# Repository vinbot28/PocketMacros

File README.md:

# PocketMacros
A minimalist macro pad with 11 switches, a rotary encoder, and a display 0.91in OLED.

## CAD
Case was designed in onshape, and the macropad uses a "budget" gasket style mount, sandwiching the PCB. Uses 4 screws to mate the top and bottom casings together.

## PCB
Here is the schematic and PCB:

## BOM
- 1x Seeed XIAO RP2040
- 11x MX-Style switches
- 12x 1N4148 diodes
- 11x Blank DSA keycaps
- 1x 0.91 inch OLED display
- 1x EC11 Rotary encoder
- 4x M3x5mx4mm heat set inserts
- 4x M3x12mm screws (owned)

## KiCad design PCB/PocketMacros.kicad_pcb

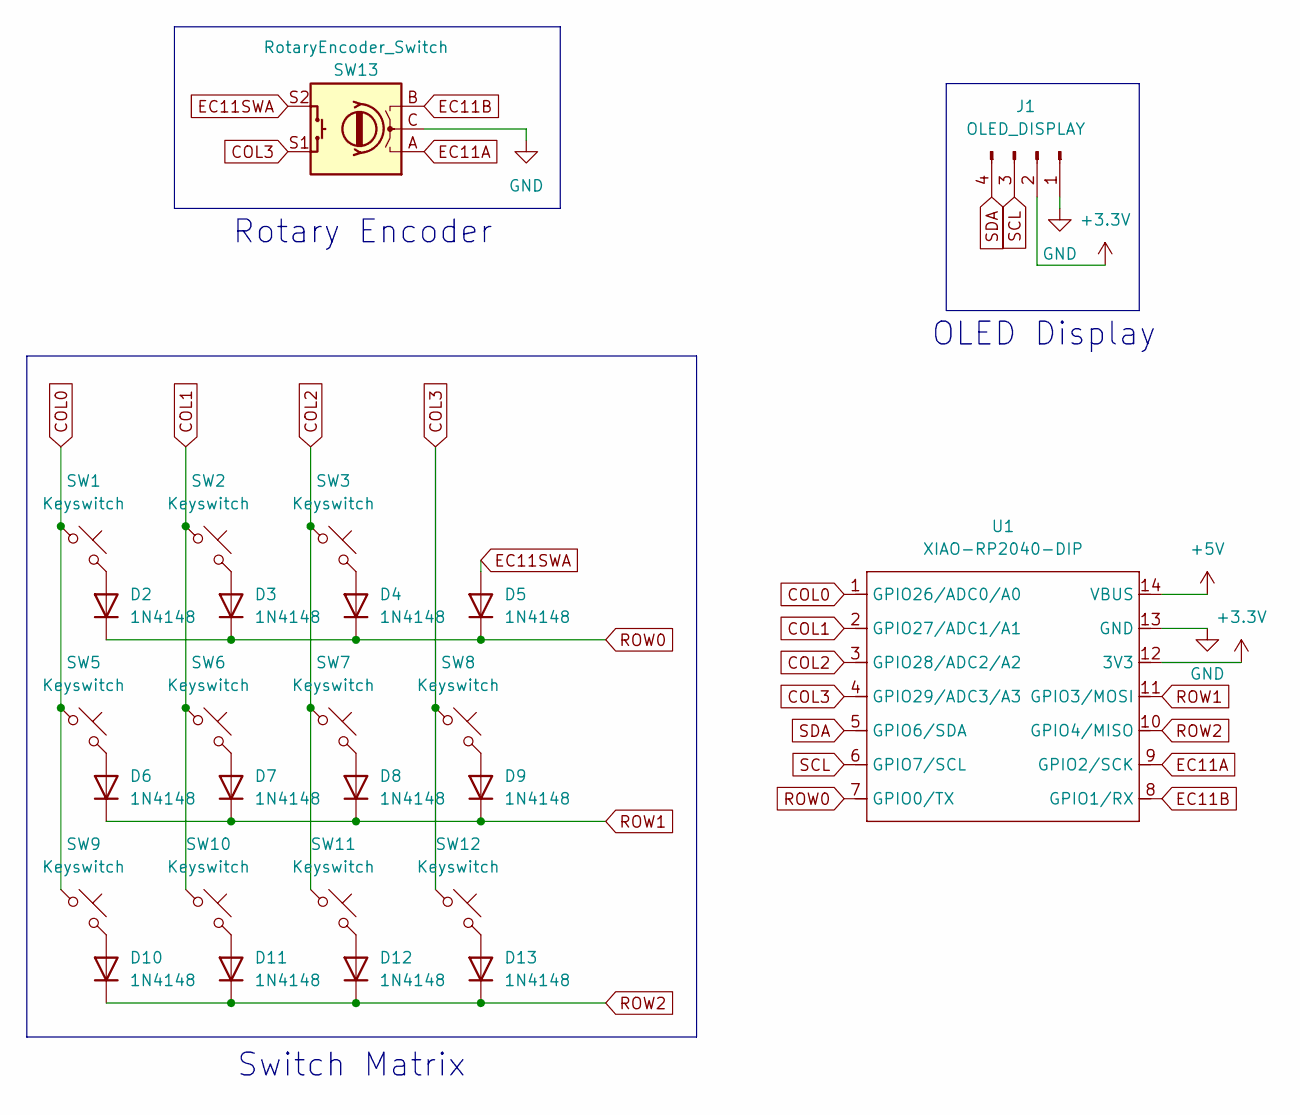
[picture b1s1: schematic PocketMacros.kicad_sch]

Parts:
D2, D3, D4, D5, D6, D7, D8, D9, D10, D11, D12, D13: 1N4148; D_DO-35_SOD27_P7.62mm_Horizontal
J1: OLED_DISPLAY; SSD1306-0.91-OLED-4pin-128x32
SW1, SW2, SW3, SW5, SW6, SW7, SW8, SW9, SW10, SW11, SW12: Keyswitch; SW_Cherry_MX_1.00u_PCB
SW13: RotaryEncoder_Switch; RotaryEncoder_Alps_EC11E-Switch_Vertical_H20mm
U1: XIAO-RP2040-DIP

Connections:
+3.3V: J1.2, U1.12 (3V3)
+5V: U1.14 (VBUS)
COL0: SW1.1, SW5.1, SW9.1, U1.1 (GPIO26/ADC0/A0)
COL1: SW2.1, SW6.1, SW10.1, U1.2 (GPIO27/ADC1/A1)
COL2: SW3.1, SW7.1, SW11.1, U1.3 (GPIO28/ADC2/A2)
COL3: SW8.1, SW12.1, SW13.S1, U1.4 (GPIO29/ADC3/A3)
EC11A: SW13.A, U1.9 (GPIO2/SCK)
EC11B: SW13.B, U1.8 (GPIO1/RX)
EC11SWA: D5.2 (A), SW13.S2
GND: J1.1, SW13.C, U1.13 (GND)
unnamed: D2.2 (A), SW1.2
unnamed: D3.2 (A), SW2.2
unnamed: D4.2 (A), SW3.2
unnamed: D6.2 (A), SW5.2
unnamed: D7.2 (A), SW6.2
unnamed: D8.2 (A), SW7.2
unnamed: D9.2 (A), SW8.2
unnamed: D10.2 (A), SW9.2
unnamed: D11.2 (A), SW10.2
unnamed: D12.2 (A), SW11.2
unnamed: D13.2 (A), SW12.2
ROW0: D2.1 (K), D3.1 (K), D4.1 (K), D5.1 (K), U1.7 (GPIO0/TX)
ROW1: D6.1 (K), D7.1 (K), D8.1 (K), D9.1 (K), U1.11 (GPIO3/MOSI)
ROW2: D10.1 (K), D11.1 (K), D12.1 (K), D13.1 (K), U1.10 (GPIO4/MISO)
SCL: J1.3, U1.6 (GPIO7/SCL)
SDA: J1.4, U1.5 (GPIO6/SDA)

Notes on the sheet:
Rotary Encoder
OLED Display
Switch Matrix

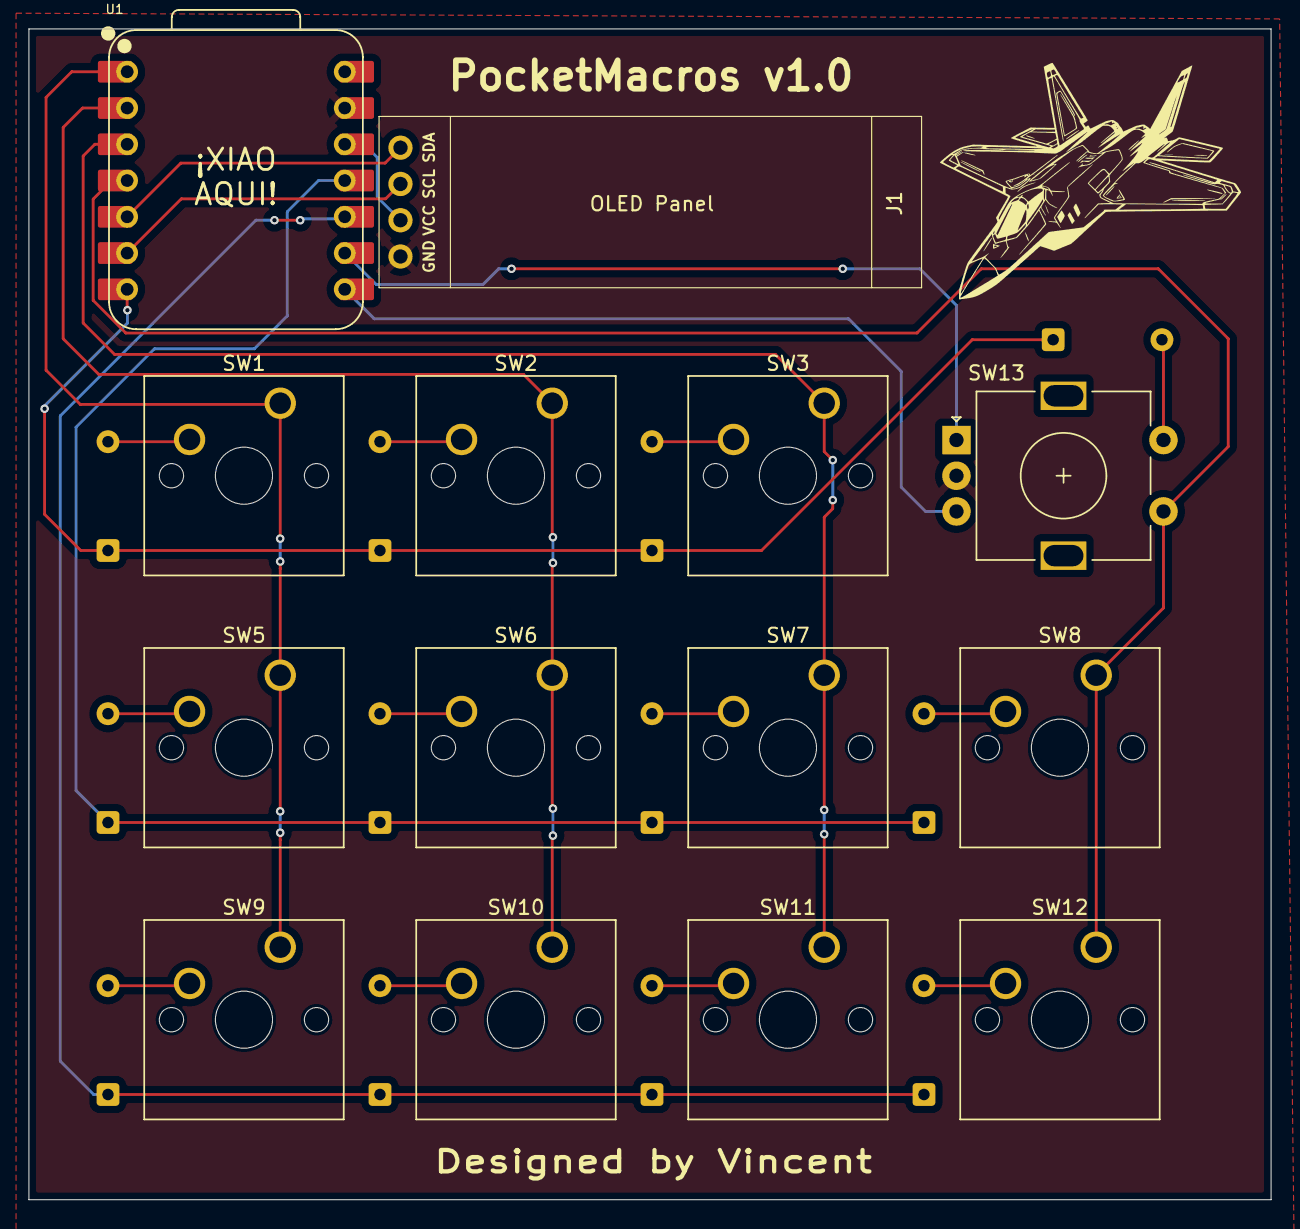
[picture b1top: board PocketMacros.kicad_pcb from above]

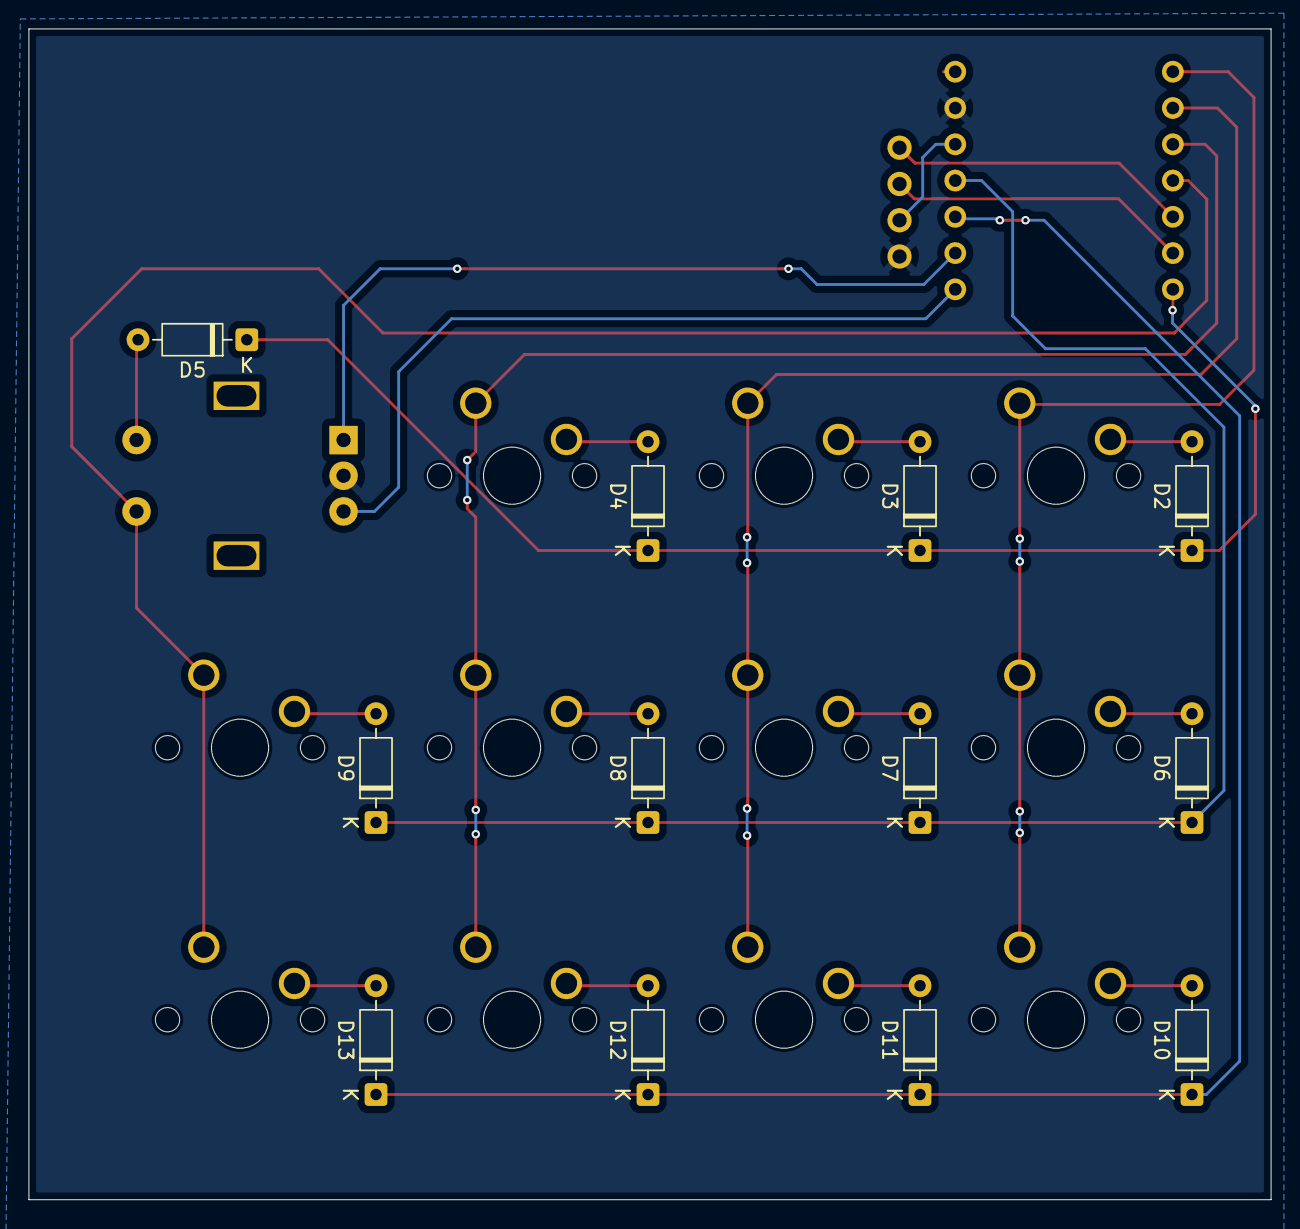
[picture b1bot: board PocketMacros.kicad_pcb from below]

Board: 2 copper layers, 87.0 x 82.0 mm, 26 parts (12 on the bottom side), 25 nets.

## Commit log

2025-07-07 added files
2025-07-07 production boom
2025-07-07 more files
